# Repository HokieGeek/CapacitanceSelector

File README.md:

# CapacitanceSelector
Decided to build a box to be able to select various capacitors to go along with my resistance decade box

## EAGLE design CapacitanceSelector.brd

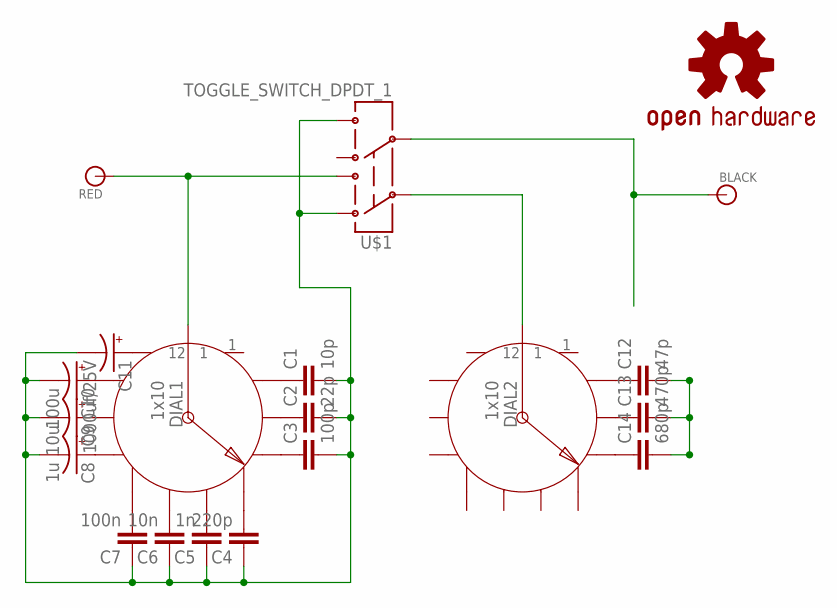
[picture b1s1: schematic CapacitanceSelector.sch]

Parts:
BLACK: BANANA_CONN
C1: 10p; CAP-PTH-SMALL-KIT
C2: 22p; CAP-PTH-SMALL-KIT
C3: 100p; CAP-PTH-SMALL-KIT
C4: 220p; CAP-PTH-SMALL-KIT
C5: 1n; CAP-PTH-SMALL-KIT
C6: 10n; CAP-PTH-SMALL-KIT
C7: 100n; CAP-PTH-SMALL-KIT
C8: 1u; CPOL-RADIAL-10UF-25V-KIT
C9: 10u; CPOL-RADIAL-10UF-25V-KIT
C10: 100u; CPOL-RADIAL-10UF-25V-KIT
C11: 1000uf/25V; CPOL-RADIAL-1000UF-25V-KIT
C12: 47p; AXIAL-5MM
C13: 470p; CAP-PTH-SMALL-KIT
C14: 680p; CAP-PTH-SMALL-KIT
DIAL1, DIAL2: 1x10; ROTARY_SWITCH_1X12
LOGO1: OSHW-LOGOL; OSHW-LOGO-L
RED: BANANA_CONN
U$1: TOGGLE_SWITCH_DPDT_1; TOGGLE_SWITCH_1

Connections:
unnamed: DIAL1.COMMON, RED.P$1, U$1.P$2 (3)
unnamed: C12.P$1 (1), DIAL2.2
unnamed: BLACK.P$1, U$1.P$4 (5)
unnamed: DIAL2.COMMON, U$1.P$3 (2)
unnamed: C5.2, DIAL1.6
unnamed: C1.1, DIAL1.2
unnamed: C2.1, DIAL1.3
unnamed: C3.1, DIAL1.4
unnamed: C4.2, DIAL1.5
unnamed: C6.2, DIAL1.7
unnamed: C13.1, DIAL2.3
unnamed: C1.2, C2.2, C3.2, C4.1, C5.1, C6.1, C7.1, C8.2 (-), C9.2 (-), C10.2 (-), C11.-, U$1.P$1 (1), U$1.P$6 (6)
unnamed: C8.1 (+), DIAL1.9
unnamed: C12.P$2 (2), C13.2, C14.2
unnamed: C14.1, DIAL2.4
unnamed: C11.+, DIAL1.12
unnamed: C7.2, DIAL1.8
unnamed: C10.1 (+), DIAL1.11
unnamed: C9.1 (+), DIAL1.10

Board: 2 copper layers, 20 parts (0 on the bottom side), 19 nets, no tracks yet.

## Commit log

2015-12-09 Initial something
2015-12-19 Moving forward with it
2015-12-20 This is going to be an overly expensive board

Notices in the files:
parts and their libraries:
SparkFun-Connectors: Licensing: Creative Commons ShareAlike 4.0 International - https://creativecommons.org/licenses/by-sa/4.0
